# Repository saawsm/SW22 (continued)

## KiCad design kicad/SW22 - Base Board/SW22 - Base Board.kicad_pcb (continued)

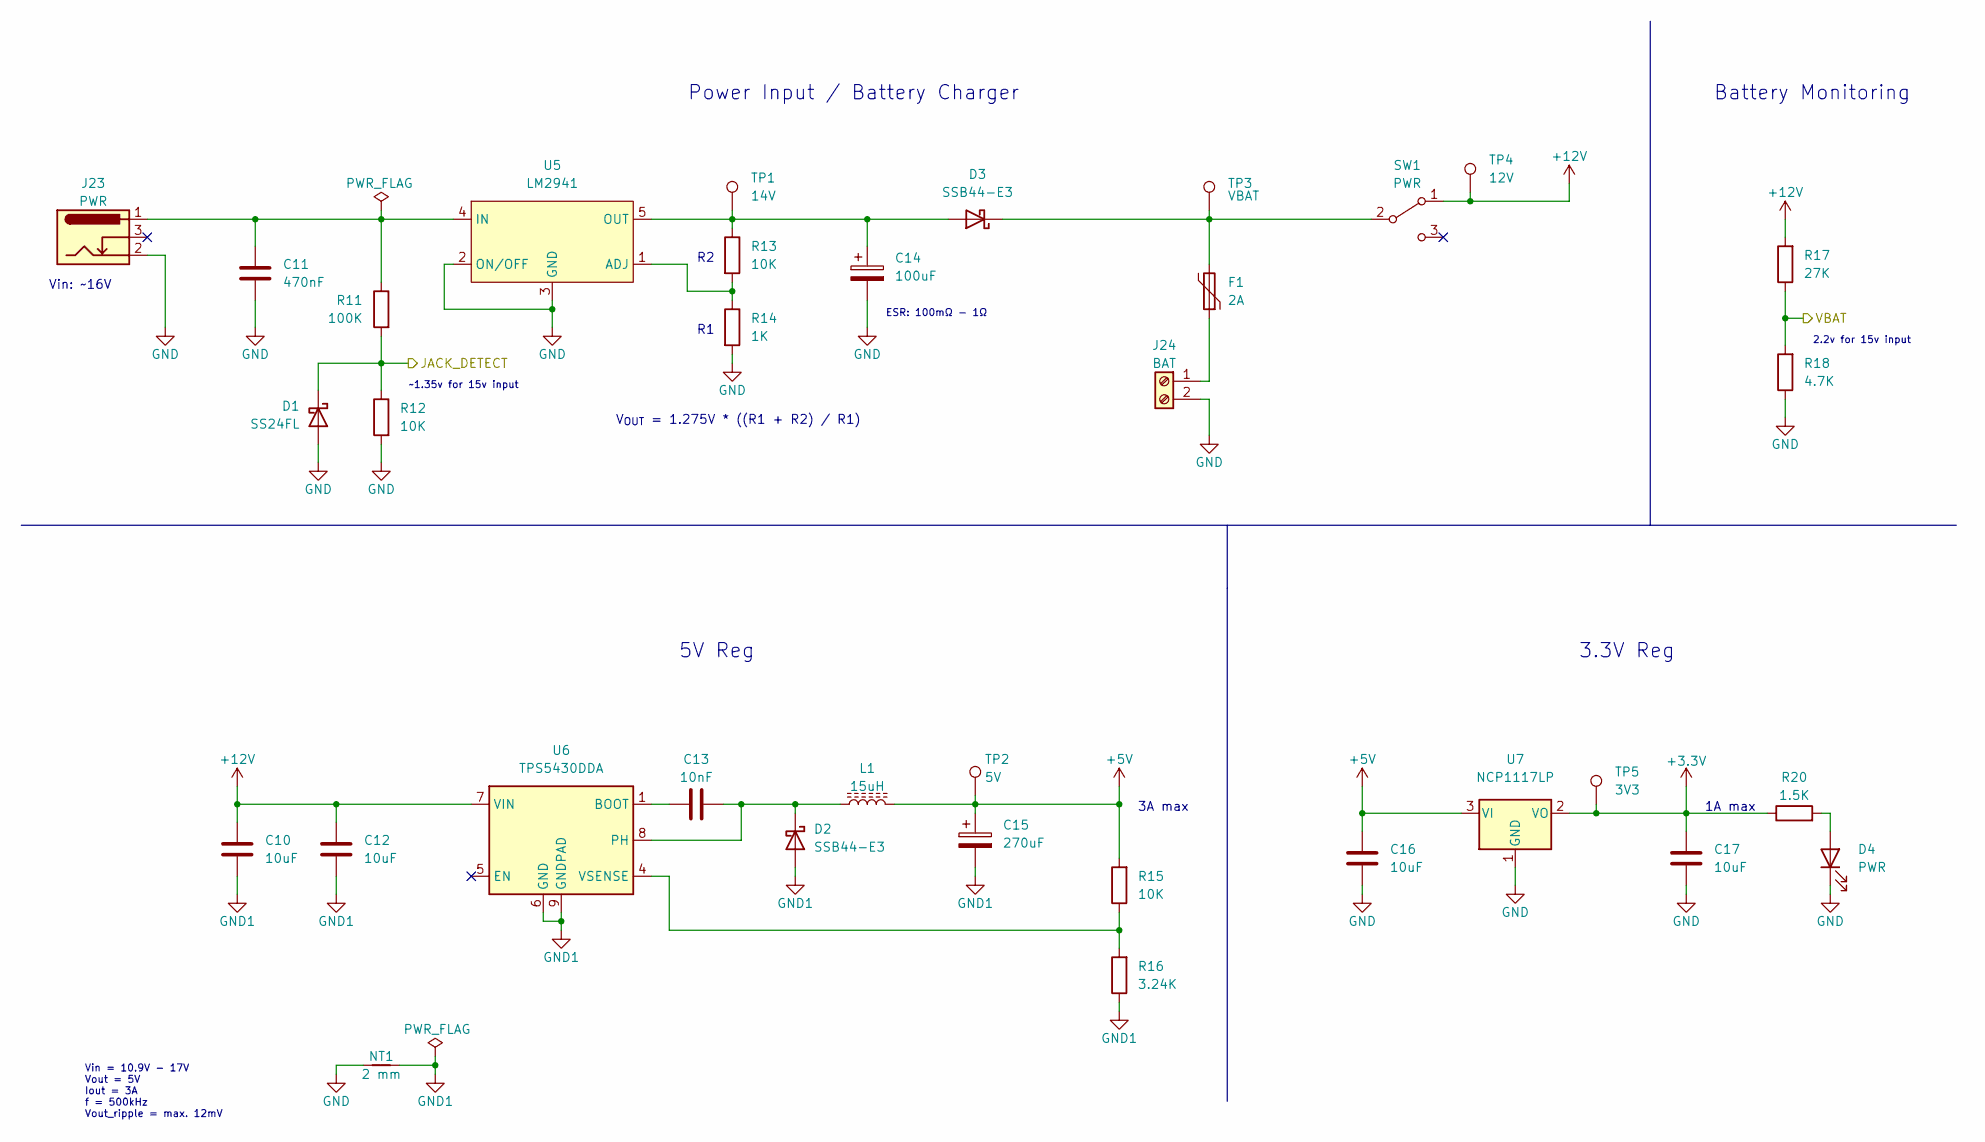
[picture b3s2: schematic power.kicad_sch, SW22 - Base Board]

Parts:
C10, C12: 10uF; C_1210_3225Metric; MPN CL32A106KBJNNNE; LCSC C380537
C11: 470nF; C_0603_1608Metric; MPN CL10A474KB8NNNC; LCSC C170149
C13: 10nF; C_0603_1608Metric; MPN CL10B103KB8NNNC; LCSC C1589
C14: 100uF; CP_Radial_D6.3mm_P2.50mm; MPN EEU-FM1E101; LCSC C1579509
C15: 270uF; CP_Elec_8x6.9; MPN 16SVPF270M; LCSC C136278
C16, C17: 10uF; C_0603_1608Metric; MPN CL10A106MA8NRNC; LCSC C96446
D1: SS24FL; D_SOD-123F; MPN SS24FL; LCSC C894433
D2: SSB44-E3; D_SMB; MPN SSB44-E3/52T; MOUSER 625-SSB44-E3
D3: SSB44-E3; D_SMB; MPN SSB44-E3/52T; LCSC C466999
D4: PWR; LED_0603_1608Metric; MPN 150060VS75000; MOUSER 710-150060VS75000
F1: 2A; Fuse_Littelfuse-LVR200; MPN LVR200S-240; LCSC C1562345
J23: PWR; BarrelJack_CUI_PJ-102AH_Horizontal; MPN PJ-102AH; MOUSER 490-PJ-102AH
J24: BAT; JST_XH_B2B-XH-A_1x02_P2.50mm_Vertical
L1: 15uH; L_Bourns_SRR1260; MPN SRR1260-150M; MOUSER 652-SRR1260-150M
NT1: 2 mm; NetTie-2_SMD_Pad2.0mm
R11: 100K; R_0603_1608Metric; MPN RC0603FR-07100KL; MOUSER 603-RC0603FR-07100KL
R12, R13, R15: 10K; R_0603_1608Metric; MPN RC0603FR-0710KL; MOUSER 603-RC0603FR-0710KL
R14: 1K; R_0603_1608Metric; MPN RC0603FR-071KL; MOUSER 603-RC0603FR-071KL
R16: 3.24K; R_0603_1608Metric; MPN RC0603FR-073K24L; LCSC C273779
R17: 27K; R_0603_1608Metric; MPN RC0603FR-0727KL; MOUSER 603-RC0603FR-0727KL
R18: 4.7K; R_0603_1608Metric; MPN RC0603FR-074K7L; MOUSER 603-RC0603FR-074K7L
R20: 1.5K; R_0603_1608Metric; MPN RC0603FR-071K5L; MOUSER 603-RC0603FR-071K5L
SW1: PWR; 500SSP1S2M6QEA; MPN 500SSP1S2M6QEA; MOUSER 612-500-A261
TP1: 14V; TestPoint_Pad_D1.5mm
TP2: 5V; TestPoint_Pad_D1.5mm
TP3: VBAT; TestPoint_Pad_D1.5mm
TP4: 12V; TestPoint_Pad_D1.5mm
TP5: 3V3; TestPoint_Pad_D1.5mm
U5: LM2941; TO-263-5_TabPin3; MPN LM2941CSX/NOPB; LCSC C512759
U6: TPS5430DDA; TI_SO-PowerPAD-8_ThermalVias; MPN TPS5430DDAR; LCSC C9864
U7: NCP1117LP; SOT-223-3_TabPin2; MPN NCP1117LPST33T3G; LCSC C146799

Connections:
+3.3V: C17.1, R20.1, TP5.1, U7.2 (VO); also elsewhere on the board
+5V: C15.1, C16.1, L1.2, R15.2, TP2.1, U7.3 (VI); also elsewhere on the board
+12V: C10.2, C12.2, R17.2, SW1.1 (A), TP4.1, U6.7 (VIN); also elsewhere on the board
/JCK_SEN: D1.1 (K), R11.2, R12.1; also elsewhere on the board
/VBAT: R17.1, R18.2; also elsewhere on the board
GND: C11.2, C14.2, C16.2, C17.2, D1.2 (A), D4.1 (K), J23.2, J24.2, NT1.2, R12.2, R14.2, R18.1, U5.2 (ON/OFF), U5.3 (GND), U7.1 (GND); also elsewhere on the board
GND1: C10.1, C12.1, C15.2, D2.2 (A), NT1.1, R16.1, U6.6 (GND), U6.9 (GNDPAD)
unnamed: C11.1, J23.1, R11.1, U5.4 (IN)
unnamed: C13.1, U6.1 (BOOT)
unnamed: C13.2, D2.1 (K), L1.1, U6.8 (PH)
unnamed: C14.1, D3.2 (A), R13.1, TP1.1, U5.5 (OUT)
unnamed: D3.1 (K), F1.2, SW1.2 (B), TP3.1
unnamed: D4.2 (A), R20.2
unnamed: F1.1, J24.1
unnamed: R13.2, R14.1, U5.1 (ADJ)
unnamed: R15.1, R16.2, U6.4 (VSENSE)

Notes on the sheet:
Vin = 10.9V - 17V Vout = 5V Iout = 3A f = 500kHz Vout_ripple = max. 12mV
V_{OUT} = 1.275V * ((R1 + R2) / R1)
ESR: 100mΩ - 1Ω
Battery Monitoring
2.2v for 15v input
~1.35v for 15v input
Vin: ~16V
3.3V Reg
Power Input / Battery Charger
5V Reg
3A max
1A max

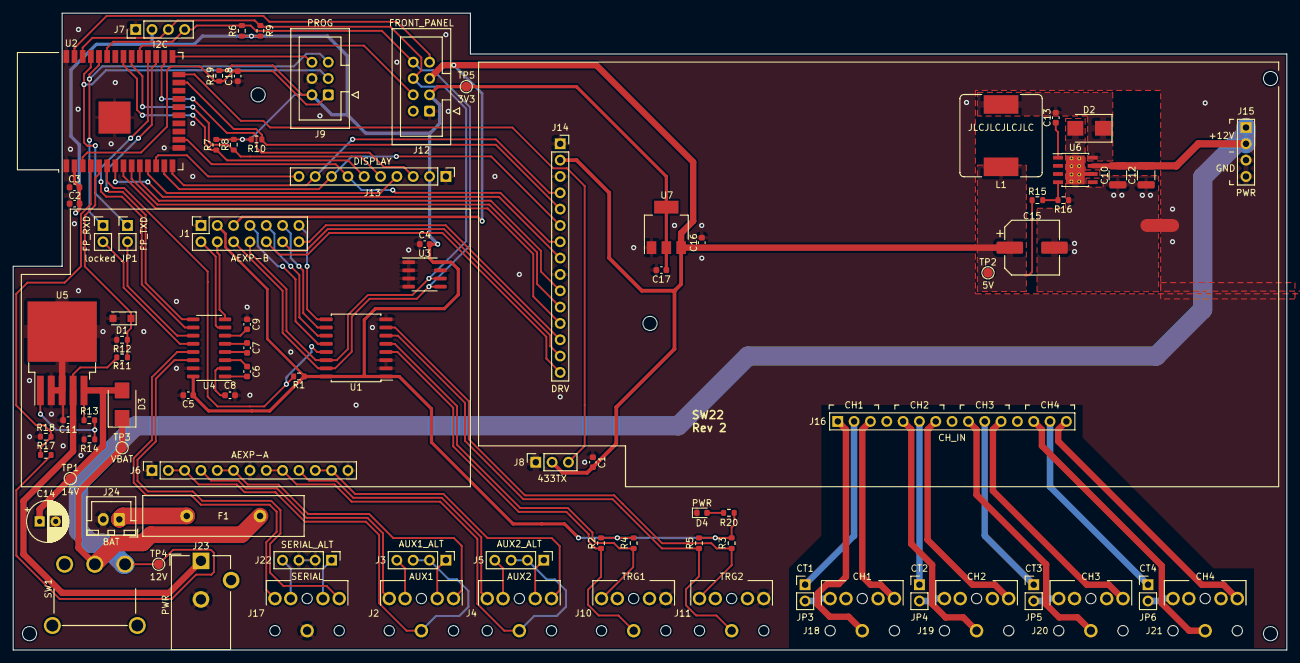
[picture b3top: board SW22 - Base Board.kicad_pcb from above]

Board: 2 copper layers, 198.1 x 99.1 mm, 93 parts (0 on the bottom side), 92 nets.

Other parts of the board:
locked: FP_RXD; PinHeader_1x02_P2.54mm_Vertical

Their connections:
/RXD0: locked.1 (A); also elsewhere on the board
unnamed 89: locked.2 (B); also elsewhere on the board

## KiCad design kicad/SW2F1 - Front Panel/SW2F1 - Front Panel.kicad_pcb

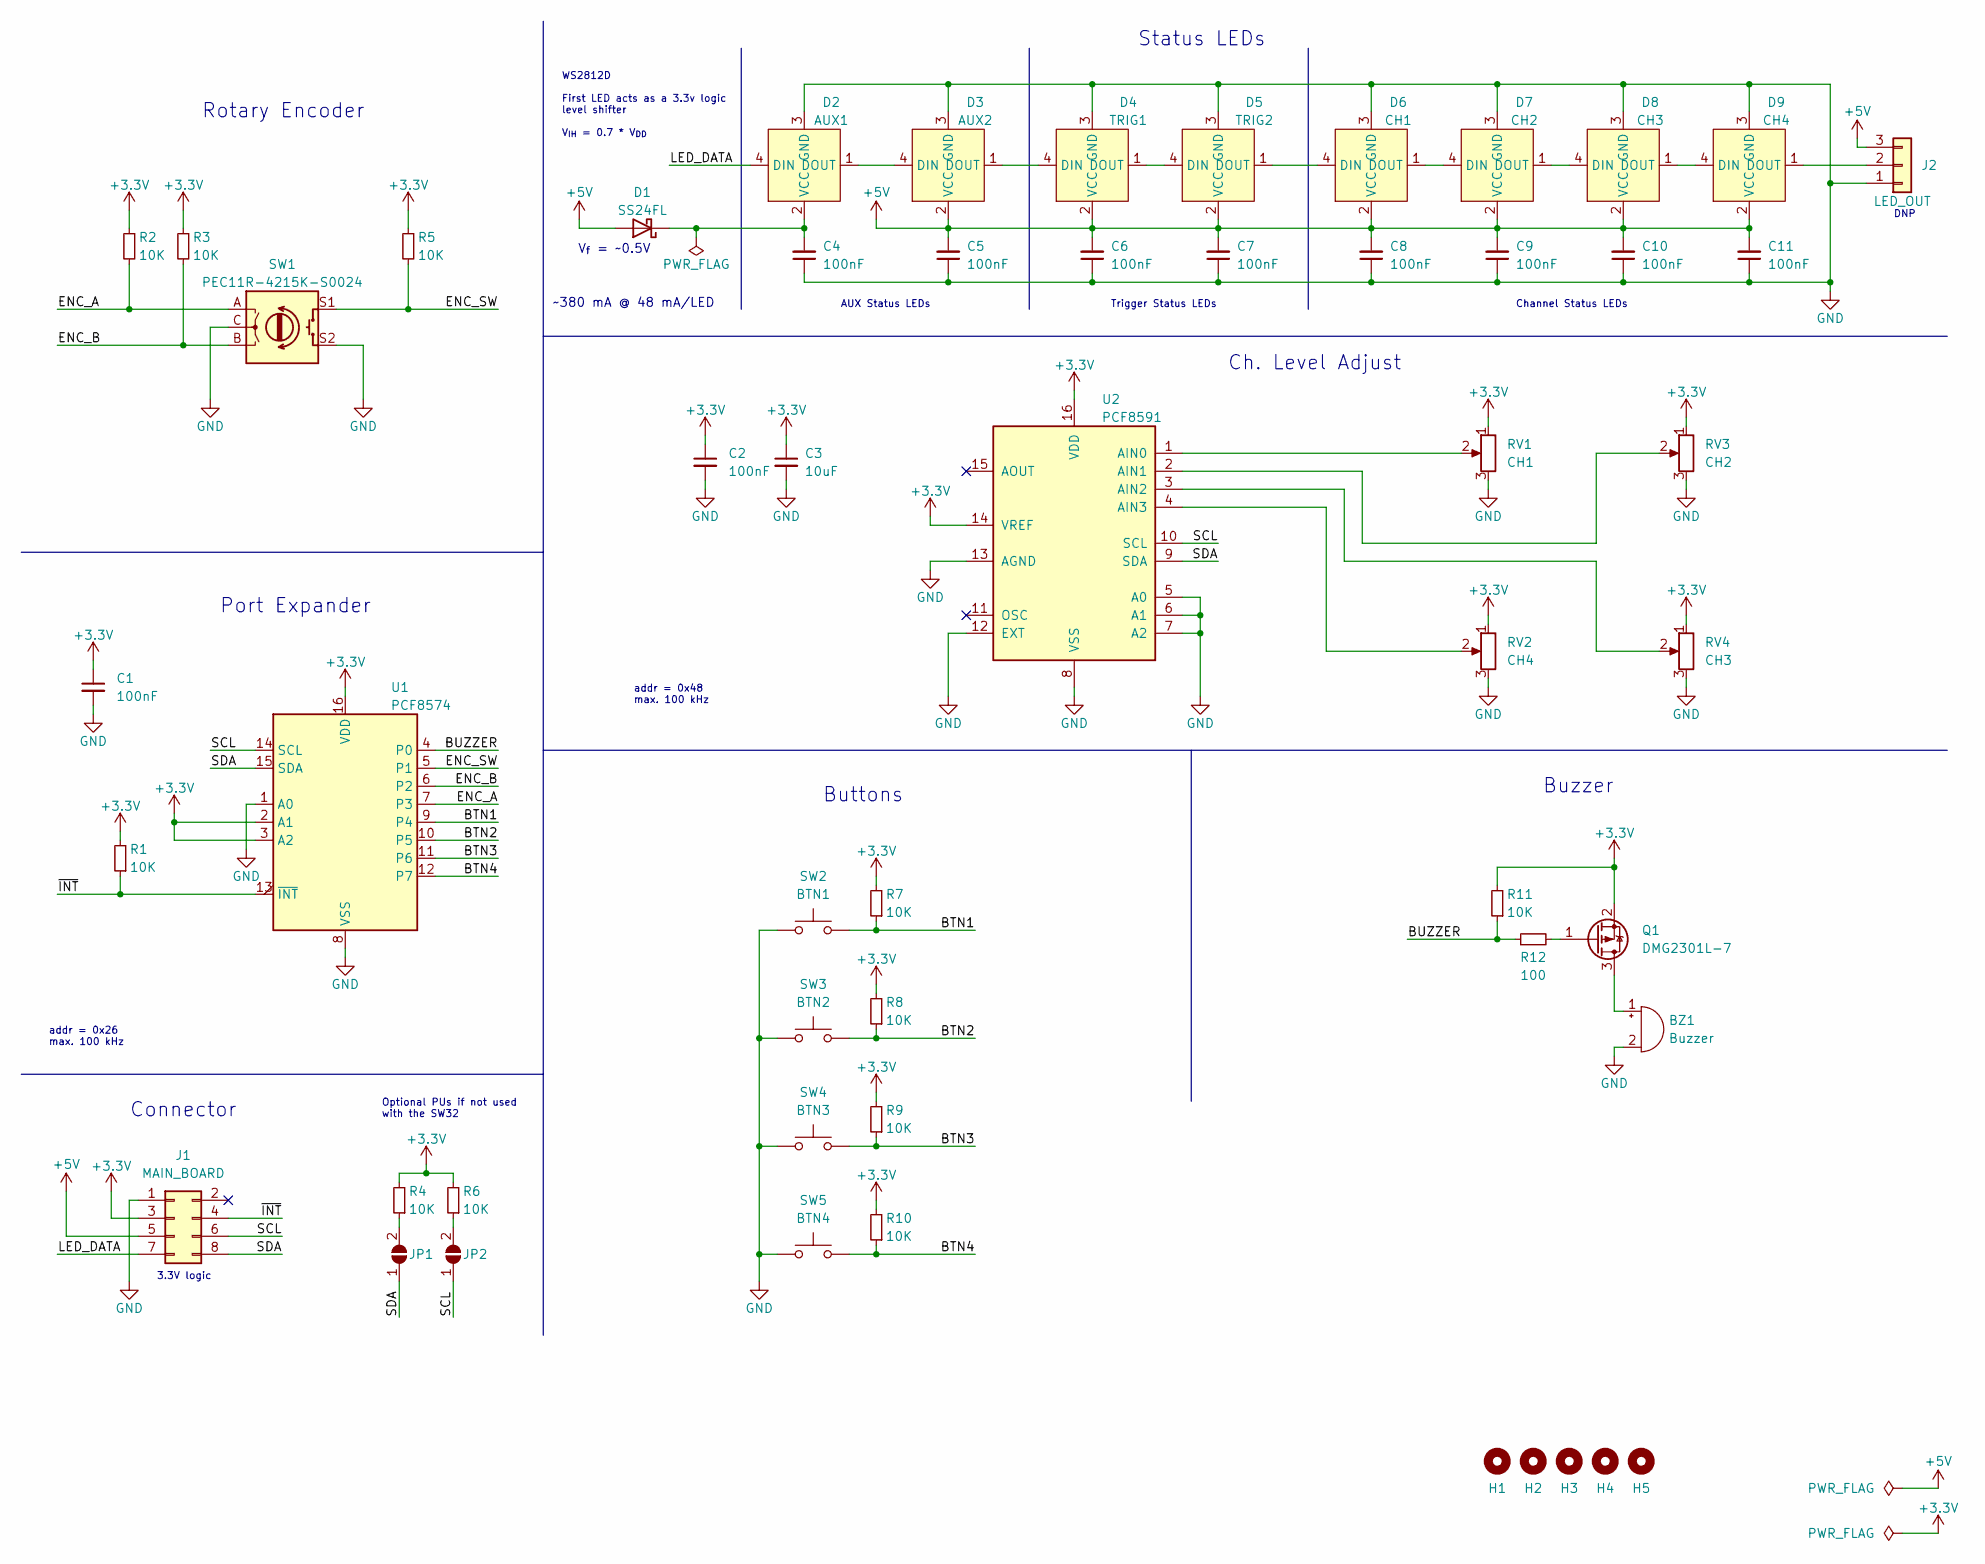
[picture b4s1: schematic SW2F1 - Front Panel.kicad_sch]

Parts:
BZ1: Buzzer; Buzzer_12x9.5RM7.6; MPN IE122303-1; MOUSER 497-IE122303-1
C1, C2, C4, C5, C6, C7, C8, C9, C10, C11: 100nF; C_0603_1608Metric; MPN CL10B104KB8NNNC; LCSC C1591
C3: 10uF; C_0603_1608Metric; MPN CL10A106MA8NRNC; LCSC C96446
D1: SS24FL; D_SOD-123F; MPN SS24FL; MOUSER 512-SS24FL
D2: AUX1; WS2812D-F5; MPN WS2812D-F5; LCSC C190565
D3: AUX2; WS2812D-F5; MPN WS2812D-F5; LCSC C190565
D4: TRIG1; WS2812D-F5; MPN WS2812D-F5; LCSC C190565
D5: TRIG2; WS2812D-F5; MPN WS2812D-F5; LCSC C190565
D6: CH1; WS2812D-F5; MPN WS2812D-F5; LCSC C190565
D7: CH2; WS2812D-F5; MPN WS2812D-F5; LCSC C190565
D8: CH3; WS2812D-F5; MPN WS2812D-F5; LCSC C190565
D9: CH4; WS2812D-F5; MPN WS2812D-F5; LCSC C190565
H1, H2, H3, H4, H5: MountingHole; MountingHole_2.2mm_M2
J1: MAIN_BOARD; IDC-Header_2x04_P2.54mm_Vertical
J2: LED_OUT; PinHeader_1x03_P2.54mm_Vertical
JP1, JP2: SolderJumper_2_Open; SolderJumper-2_P1.3mm_Open_RoundedPad1.0x1.5mm
Q1: DMG2301L-7; SOT-23; MPN DMG2301L-7; LCSC C102619
R1, R2, R3, R4, R5, R6, R7, R8, R9, R10, R11: 10K; R_0603_1608Metric; MPN RC0603FR-0710KL; LCSC C98220
R12: 100; R_0603_1608Metric; MPN RC0603FR-07100RL; MOUSER 603-RC0603FR-07100RL
RV1: CH1; Potentiometer_Bourns_PTV09A-1_Single_Vertical; MPN PTV09A-4020S-B103
RV2: CH4; Potentiometer_Bourns_PTV09A-1_Single_Vertical; MPN PTV09A-4020S-B103
RV3: CH2; Potentiometer_Bourns_PTV09A-1_Single_Vertical; MPN PTV09A-4020S-B103
RV4: CH3; Potentiometer_Bourns_PTV09A-1_Single_Vertical; MPN PTV09A-4020S-B103
SW1: PEC11R-4215K-S0024; Rotary_Encoder_Switched_PEC11R; MPN PEC11R-4215K-S0024
SW2: BTN1; D6C; MPN D6C90F2LFS; MOUSER 611-D6C90F2LFS
SW3: BTN2; D6C; MPN D6C90F2LFS; MOUSER 611-D6C90F2LFS
SW4: BTN3; D6C; MPN D6C90F2LFS; MOUSER 611-D6C90F2LFS
SW5: BTN4; D6C; MPN D6C90F2LFS; MOUSER 611-D6C90F2LFS
U1: PCF8574; SOIC-16W_7.5x10.3mm_P1.27mm; MPN PCF8574T/3,512; LCSC C1522621
U2: PCF8591; SOIC-16W_7.5x10.3mm_P1.27mm; MPN PCF8591T/2,518; MOUSER 771-PCF8591TD-T

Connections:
+3.3V: C1.1, C2.1, C3.1, J1.3, Q1.2 (S), R1.2, R2.1, R3.1, R4.2, R5.1, R6.2, R7.2, R8.2, R9.2, R10.2, R11.2, RV1.1, RV2.1, RV3.1, RV4.1, U1.2 (A1), U1.3 (A2), U1.16 (VDD), U2.14 (VREF), U2.16 (VDD); also elsewhere on the board
+5V: C5.2, C6.2, C7.2, C8.2, C9.2, C10.2, C11.2, D1.2 (A), D3.2 (VCC), D4.2 (VCC), D5.2 (VCC), D6.2 (VCC), D7.2 (VCC), D8.2 (VCC), D9.2 (VCC), J1.5, J2.3
/BTN1: R7.1, SW2.2, U1.9 (P4)
/BTN2: R8.1, SW3.2, U1.10 (P5); also elsewhere on the board
/BTN3: R9.1, SW4.2, U1.11 (P6)
/BTN4: R10.1, SW5.2, U1.12 (P7)
/BUZZER: R11.1, R12.1, U1.4 (P0)
/ENC_A: R2.2, SW1.A, U1.7 (P3)
/ENC_B: R3.2, SW1.B, U1.6 (P2)
/ENC_SW: R5.2, SW1.S1, U1.5 (P1)
/LED_DATA: D2.4 (DIN), J1.7
/SCL: J1.6, JP2.1 (A), U1.14 (SCL), U2.10 (SCL)
/SDA: J1.8, JP1.1 (A), U1.15 (SDA), U2.9 (SDA)
/~INT: J1.4, R1.1, U1.13 (~INT)
GND: BZ1.2 (+), C1.2, C2.2, C3.2, C4.1, C5.1, C6.1, C7.1, C8.1, C9.1, C10.1, C11.1, D2.3 (GND), D3.3 (GND), D4.3 (GND), D5.3 (GND), D6.3 (GND), D7.3 (GND), D8.3 (GND), D9.3 (GND), J1.1, J2.1, RV1.3, RV2.3, RV3.3, RV4.3, SW1.C, SW1.S2, SW2.1, SW3.1, SW4.1, SW5.1, U1.1 (A0), U1.8 (VSS), U2.5 (A0), U2.6 (A1), U2.7 (A2), U2.8 (VSS), U2.12 (EXT), U2.13 (AGND)
unnamed: BZ1.1 (-), Q1.3 (D)
unnamed: C4.2, D1.1 (K), D2.2 (VCC)
unnamed: D2.1 (DOUT), D3.4 (DIN)
unnamed: D3.1 (DOUT), D4.4 (DIN)
unnamed: D4.1 (DOUT), D5.4 (DIN)
unnamed: D5.1 (DOUT), D6.4 (DIN)
unnamed: D6.1 (DOUT), D7.4 (DIN)
unnamed: D7.1 (DOUT), D8.4 (DIN)
unnamed: D8.1 (DOUT), D9.4 (DIN)
unnamed: D9.1 (DOUT), J2.2
unnamed: JP1.2 (B), R4.1
unnamed: JP2.2 (B), R6.1
unnamed: Q1.1 (G), R12.2
unnamed: RV1.2, U2.1 (AIN0)
unnamed: RV2.2, U2.4 (AIN3)
unnamed: RV3.2, U2.2 (AIN1)
unnamed: RV4.2, U2.3 (AIN2)

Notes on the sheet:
~380 mA @ 48 mA/LED
Channel Status LEDs
AUX Status LEDs
Ch. Level Adjust
3.3V logic
Port Expander
Buttons
DNP
Status LEDs
Optional PUs if not used with the SW32
addr = 0x48 max. 100 kHz
V_{f} = ~0.5V
Trigger Status LEDs
Buzzer
Rotary Encoder
Connector
addr = 0x26 max. 100 kHz
WS2812D First LED acts as a 3.3v logic level shifter V_{IH} = 0.7 * V_{DD}

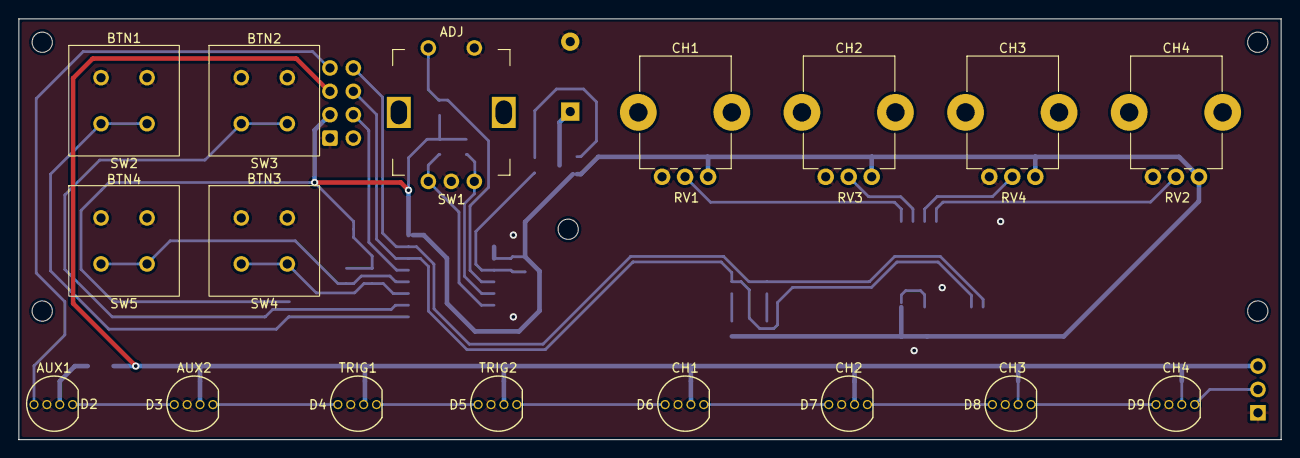
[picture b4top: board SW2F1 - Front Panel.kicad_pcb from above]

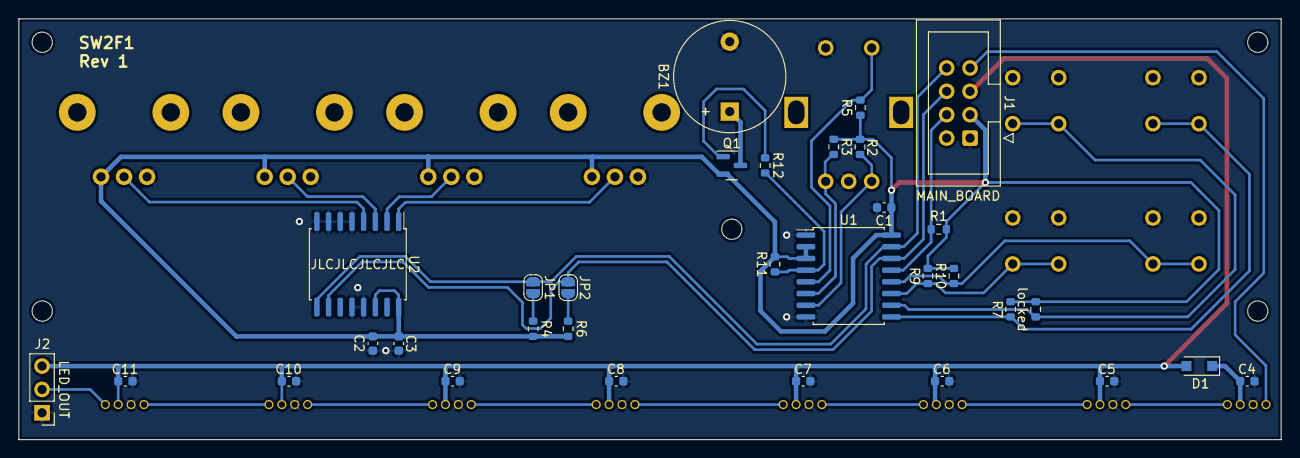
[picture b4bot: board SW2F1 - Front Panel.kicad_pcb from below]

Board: 2 copper layers, 137.2 x 45.7 mm, 54 parts (32 on the bottom side), 32 nets.

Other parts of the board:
locked: 10K; R_0603_1608Metric

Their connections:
+3.3V: locked.2; also elsewhere on the board
/BTN2: locked.1; also elsewhere on the board

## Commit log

2022-01-30 cleanup
2022-01-30 move to project folder
2022-01-30 add initial SW-3221 design
2022-01-30 use io5 for encoder switch
2022-01-31 update part numbers
2022-01-31 refactor
2022-01-31 fix link
2022-02-02 make SW-3240 modular
2022-02-02 add basic audio module
2022-02-02 add basic front panel module
2022-02-02 add basic output board
2022-02-02 update dru
2022-02-03 ignore auto saves
2022-02-03 split dual esp32 modules
2022-02-04 add main mcu to front panel
2022-02-04 add schematic pdfs
2022-02-04 fix footprint pin mismatch
2022-02-04 update pdf
2022-02-06 many changes
2022-02-06 add schematic link shortcuts
2022-02-07 use 5v for front panel connector
2022-02-22 use atmega328pb for main board
2022-04-07 major changes
2022-04-08 excluded bom items
2022-06-13 redesign
2022-06-13 rename
2022-06-29 fix comments
2022-06-29 use baremetal pico
2022-06-29 update doc
2022-10-09 redesign / project restructure
2022-10-14 add wiki
2022-10-14 fix inconsistencies
2022-10-14 finalize driver board
2022-10-14 fix wrong ADC footprint
2022-10-22 align modules on the same 0.1" grid
2022-11-05 use ESP32
2022-11-07 misc. cleanup
2022-11-07 add gerbers
2022-11-08 add SW3O2
2022-11-10 add optional I2C pullups
2022-11-13 add cap
2022-11-14 rev 1
2022-12-18 rename wiki submodule
2022-12-18 remove redundant folder
2022-12-18 add MPN to ibom
2022-12-18 add pcb images
2022-12-18 update feature list
2022-12-19 update MPN for rotary encoder
2022-12-19 update MPN for pots
2022-12-19 reduce size
2022-12-20 add front cover
2022-12-20 add front panel pcb images
2022-12-20 cleanup silkscreen
2022-12-20 fixed typo
2022-12-21 update tolerances
2022-12-21 fix auto program
2022-12-21 increase spoke width for driver header
2022-12-21 simplify bom - use SS24FL
2022-12-21 add USB marker for pico
2022-12-22 add power led
2022-12-22 fix incorrect MPN
2023-01-14 move silkscreen from case edge
2023-01-26 add images
2023-06-19 fix firmware language
2023-06-19 add SW2E1
2023-06-21 remove wiki submodule
2023-06-29 add LICENSE
2023-11-11 firmware note
2024-05-21 add note
